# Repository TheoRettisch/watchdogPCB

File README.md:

# DSP Heartbeat Watchdog Board

## Purpose

This experimental board switches the 12 V amplifier remote output in a car PC
audio system. A 3.3 V heartbeat from the DSP keeps a hardware timer armed, a
separate fault input can disable the output, and an isolated sense line reports
the voltage state back to the DSP.

## Before You Build or Connect

Use an upstream fuse on the 12 V input. F1 is a resettable PTC that limits
current on the remote output. Review the behavior below and bench-test the
board before connecting an amplifier. See the [Bring-Up Checklist](#bring-up-checklist)
and [Known Limitations](#known-limitations).

### Connector Summary

| Connector | Pin or terminal | Net | Function |
|---|---|---|---|
| J1 | Pin 1 | `DSP_HB_3V3` | 3.3 V heartbeat from the DSP |
| J1 | Pin 2 | `DSP_GND` | Shared DSP-side return for heartbeat, fault, and sense |
| J2 | Pin 1 | `DSP_FAULT_IN` | Fault GPIO, driven low when healthy |
| J2 | Pin 2 | `DSP_3V3` | 3.3 V supply for the fault and sense pullups |
| J3 | Pin 1 | `+12V` | Fused 12 V input |
| J3 | Pin 2 | `CAR_GND` | Car or bench supply ground |
| J4 | Single wire entry | `AMP_REM` | Switched amplifier remote output |
| J5 | Single wire entry | `REMOTE_SENSE` | Active-low voltage feedback to the DSP |

J1 pin 2 is the board's only connector for `DSP_GND`. J4 and J5 each use a
Phoenix 1790490 terminal with one wire entry and two PCB solder tails on the
same net. The amplifier remote input uses the amplifier's own ground return.

### Enable and Shutdown Behavior

| Condition | Heartbeat timer | Fault clamp |
|---|---|---|
| Heartbeat edges arrive within the timeout and the fault GPIO is low | Keeps the output driver enabled | Inactive |
| Pulses stop or J1 pin 1 opens while J1 pin 2 stays connected | Switches J4 off when the timer expires | Remains available with DSP supply and ground intact |
| Fault GPIO goes high or Hi-Z, or its signal wire opens, with `DSP_3V3` and `DSP_GND` intact | Continues to follow heartbeat edges | U2 clamps the driver and switches J4 off |
| Control process crashes or exits, or the DSP reboots | Times out if heartbeat edges stop | Depends on the GPIO state. A pin still driving low leaves the clamp inactive |
| **J1 ground return opens**, including when both J1 wires are disconnected | Times out after the last trigger | Loss of `DSP_GND` can release an active clamp and briefly turn J4 on while the timer is still armed |
| **Complete J2 disconnection**, with on-board R12 as the only pullup on J5 | Can keep J4 on as long as heartbeat edges continue | U2 loses its input drive and any active clamp releases |
| Board unpowered or `+5V` absent | Timer inactive. R9 defaults Q1 off | — |
| Heartbeat held high at power-on, fault clamp inactive | Reset release can trigger one output pulse. See [Hardware Timeout](#hardware-timeout) | Inactive |

With J2 disconnected and U3 off, an additional pullup on J5, including the
DSP GPIO's internal pullup, can feed the U2 LED through R12, R10, and R11.
Whether that current can hold the fault clamp active depends on the pullup
strength.

## Project Status and Publication Scope

The author designed and hand-assembled REV 01 for a private installation and
shares the design free of charge. No boards, kits, or services are offered. The
design is licensed under `CERN-OHL-S-2.0`, which allows commercial use under its
terms. See [License](#license) and [Validation Status and Scope](#validation-status-and-scope).

## Project Files

- [KiCad project](dhw.kicad_pro), [schematic](dhw.kicad_sch), and [PCB layout](dhw.kicad_pcb)
- [Bill of materials](dhw.csv) with part numbers and datasheet links where available
- [Project footprints](libs/Watchdog.pretty/) for the Bourns MF-R025 and Phoenix Contact 1790490
- [Hand-built SPICE testbenches](spice/testbenches/) and [auto-generated runs](spice_runs/)

Open the project in KiCad 10 with the standard symbol and footprint libraries
installed. All schematic symbols use the standard libraries. The
[footprint library table](fp-lib-table) resolves the two local footprints
through `${KIPRJMOD}`. Those footprints reference optional STEP models under
`libs/3D_models/` that are absent from this checkout.

The companion watchdog software is maintained separately. See
[Timing Notes](#timing-notes) for the heartbeat settings used for this design

## High-Level Architecture

```mermaid
flowchart LR
    DSP["Lattepanda / DSP side\n3.3 V GPIO heartbeat"] --> J1["J1 heartbeat input"]
    J1 --> U1["U1 LTV-817\nheartbeat optocoupler"]
    U1 --> IC1["IC1 CD74HC123E\nretriggerable monostable"]
    IC1 --> Q2["Q2 2N3904\nbase/gate driver"]
    Q2 --> Q1["Q1 FQP27P06\nP-channel high-side switch"]
    Q1 --> F1["F1 MF-R025 PTC"]
    F1 --> J4["J4 amplifier remote output"]

    DSPF["DSP fault GPIO\nlow = healthy"] --> J2["J2 fault input and 3.3 V supply"]
    J2 --> U2["U2 LTV-817\nfault optocoupler"]
    U2 --> Q2

    F1 --> R13["R13 2.2 kohm"]
    R13 --> U3["U3 LTV-817\nsense optocoupler"]
    U3 --> J5["J5 remote sense output"]
    J5 --> DSPS["DSP sense GPIO\nlow = voltage detected"]

    J3["+12 V input"] --> D1["D1 P6KE22A TVS"]
    J3 --> U4["U4 L7805CV\n+5 V logic rail"]
    U4 --> IC1
```

## Functional Description

### Heartbeat Input Path

R2 (680 Ω) limits the U1 optocoupler LED current. R1 (100 kΩ) pulls the
heartbeat input low when the drive floats. When the DSP GPIO pulse goes
high, U1 pulls `HB_ISO_LOW` low on the car-ground side. R7 (47 kΩ) pulls
that node up to `+5V` between pulses. The falling edge triggers IC1.

### Hardware Timeout

IC1 is a CD74HC123E retriggerable monostable. The first monostable section is
used as the heartbeat watchdog timer.

The first section uses the following IC1 pins.

- pin 1, `~1A`: heartbeat trigger input, net `HB_ISO_LOW`
- pin 2, `1B`: tied to `+5V`
- pin 3, `~1R`: power-on reset network R5/C4 (see below)
- pin 13, `1Q`: watchdog output, net `MONO_Q`
- pin 14, `1CX`: timing capacitor node
- pin 15, `1RXCX`: timing resistor/capacitor node
- pin 16, `VCC`: `+5V`
- pin 8, `GND`: `CAR_GND`

The inputs and timing pins of the second section (`~2A`, `2B`, `~2R`, `2CX`,
and `2RXCX`) are tied to `CAR_GND`, holding it in reset. The unused outputs
(`~1Q`, `2Q`, and `~2Q`) carry no-connect flags.

R6 (220 kΩ) and C1 (1 µF, 63 V film, WIMA MKS2C041001F00JSSD) set the
nominal timeout. See [Timing Notes](#timing-notes) for the calculation and
other R6 values.

R5 (200 kΩ) and C4 (100 nF) hold `~1R` low at power-on while C4 charges. If
the heartbeat GPIO is already held high, U1 holds `~1A` low while `1B` is
high. The CD74HC123 can trigger as reset rises under those conditions. If
the fault clamp is inactive, J4 can energize for one timeout without a new
heartbeat edge. See the truth table in the
[TI CD74HC123 datasheet](https://www.ti.com/lit/ds/symlink/cd74hc123.pdf#page=2).

### Fault Input Path

The DSP is intended to drive `DSP_FAULT_IN` low only while healthy and
intentionally armed. When the GPIO floats or its signal wire opens, the
3.3 V supply feeds the U2 optocoupler LED through the R10 pullup (680 Ω) and
R11 (330 Ω). A GPIO driven high supplies current through R11 directly. With
a 1.2 V LED drop, these paths give about 2.1 mA and 6.4 mA respectively at
3.3 V.

U2 pulls `Q2_BASE` low and turns off the output driver even while the
monostable is active. Its input LED returns through `DSP_GND` on J1 pin 2.
See [Enable and Shutdown Behavior](#enable-and-shutdown-behavior) for the
effects of connector and GPIO faults.

### Remote Output Driver

The amplifier remote output is switched by Q1, a P-channel MOSFET used as a
high-side switch.

- Q1 FQP27P06
  - pad 1: gate, net `Q1_GATE`
  - pad 2: drain, net `Q1_DRAIN`
  - pad 3: source, net `+12V`
- Q2 2N3904 pulls the Q1 gate low when `MONO_Q` is high and U2 is inactive
  - pad 1: emitter, `CAR_GND`
  - pad 2: base, `Q2_BASE`
  - pad 3: collector, `Q2_COLL`
- R4: 47 kohm base feed from `MONO_Q` into Q2
- R3: 100 kohm base pulldown on `Q2_BASE`
- R9: 100 kohm gate pullup to `+12V`, defaulting Q1 off
- R8: 10 kohm between Q1 gate and Q2 collector
- Z1 BZX55C12-TAP clamps Q1 gate-source voltage
  - cathode to `+12V`
  - anode to `Q1_GATE`
- F1 MF-R025 PTC is in series with the remote output
  - F1 pin 1: `Q1_DRAIN`
  - F1 pin 2: `AMP_REM`

J4 exposes `AMP_REM` through its single wire entry. When Q2 is off, R9
returns the Q1 gate to the source rail and turns Q1 off.

### Remote Sense Feedback

R13 (2.2 kΩ) feeds the U3 optocoupler LED from `AMP_REM` after F1 (about
4.9 mA at 12 V). D2 (1N4148) clamps reverse voltage across the LED, with its
cathode at the R13/U3 node and its anode at `CAR_GND`.

J5's single wire entry carries `REMOTE_SENSE`. With `DSP_3V3` and `DSP_GND`
present, U3's open collector pulls J5 low when the post-F1 voltage is high
enough to drive the optocoupler. R12 (10 kΩ) pulls J5 high when U3 releases
it. Software can flag a mismatch between the commanded state and this
voltage indication. A tripped F1 is one possible cause of low output voltage.
The board itself takes no action based on the sense line.

Treat sense as unavailable if the DSP supply or ground is lost. With J2
unplugged and U3 off, R12 has no supply to drive J5 high, so the reading can
float or follow the receiving GPIO's bias.

## Power Architecture

- D1 (P6KE22A) clamps transients on the 12 V input. Pad 1 is the cathode on
  `+12V` and pad 2 is the anode on `CAR_GND`.
- U4 (L7805CV) generates the local `+5V` logic rail. Pins 1 through 3 are
  `+12V`, `CAR_GND`, and `+5V` respectively.
- C2 (10 µF, 63 V polymer hybrid, Würth 870575873001) provides bulk capacitance
  on `+5V`.
- C6 (470 nF, 50 V) bypasses the U4 input. C3 (100 nF) bypasses its output.
- C5 and C7 (100 nF each) bypass the IC1 supply and the 12 V switch stage,
  respectively. C4 (100 nF) belongs to the reset circuit.

C3–C7 are 1206 SMD ceramics. The other electrical components are through-hole.

## Timing Notes

The companion configuration uses 20 Hz (one trigger edge every 50 ms), a 5 ms
pulse width, and a 70 ms software jitter warning threshold. The hardware
needs one clean trigger edge per period. The software warning is a diagnostic
that depends on the process running.

At 5 V, the CD74HC123 nominal pulse width is approximately
`0.45 × R6 × C1`. With the installed 220 kΩ and 1 µF, the calculation gives
99 ms, leaving about 49 ms of nominal margin at 20 Hz. The back silkscreen
lists these R6 options for other heartbeat intervals (C1 remains 1 µF).

| Heartbeat | Period | Nominal margin with 220 kΩ | Silkscreen R6 options | Nominal timeout with those options |
|---:|---:|---:|---|---|
| 50 Hz | 20 ms | 79 ms | 91 / 130 kΩ | 41 / 59 ms |
| 25 Hz | 40 ms | 59 ms | 180 / 270 kΩ | 81 / 122 ms |
| 20 Hz | 50 ms | 49 ms | 220 / 330 kΩ | 99 / 149 ms |
| 15 Hz | 66.7 ms | 32 ms | 300 / 430 kΩ | 135 / 194 ms |
| 10 Hz | 100 ms | None | 470 / 680 kΩ | 212 / 306 ms |

Trigger gaps must stay below the actual timeout. Allow for R6/C1 tolerance,
temperature, supply variation, and scheduling jitter when selecting the
heartbeat rate and checking the assembled board.

## PCB / Fabrication Details

- Board size is 72.0 mm × 64.0 mm with two copper layers. Separate `CAR_GND`
  and `DSP_GND` pours appear on both sides.
- The layout has 31 through-hole components, five 1206 components, and four
  3.2 mm non-plated M3 mounting holes.
- The board routes 24 nets and uses 48 vias (0.60 mm diameter, 0.30 mm drill),
  mostly for ground stitching.
- The project specifies a 0.20 mm minimum track width, a 0.30 mm minimum
  through-hole drill, and a 0.15 mm minimum via annular ring.

Order bare boards for hand assembly. Typical settings are 2-layer FR-4,
1.6 mm thickness, 1 oz copper, ENIG or lead-free HASL, and electrical testing.

## Validation Status and Scope

### Saved Simulations

| Testbench | Scope and saved result |
|---|---|
| [Monostable RC model](spice/testbenches/tb_monostable_timeout.cir) | Uses the older 200 kΩ R6 and 1 µF C1. The simulated RC interval after the last discharge ends is about 90 ms. The 99 ms for the current 220 kΩ value is a nominal calculation. |
| [Gate driver](spice/testbenches/tb_gate_driver.cir) | With a generic MOSFET, an idealized Q2 switch, and a cold F1, the model gives about 10.9 V from source to gate when enabled at 12 V. |
| [Optocoupler LED drive](spice/testbenches/tb_opto_led_drive.cir) | A generic IR LED with a 680 Ω series resistor draws about 3.1 mA at 3.3 V. The model covers the U1 LED drive. It omits the U2 fault clamp and U3 sense path. |

See [Known Limitations](#known-limitations) for the hardware validation scope.

## Bring-Up Checklist

### Bench Checks

1. With the amplifier disconnected, inspect solder joints and verify diode
   and transistor orientation. D1's cathode goes to `+12V`. D2's cathode goes
   to the R13/U3 node. Q1 pads 1 through 3 are gate, drain, and source.
2. Connect the DSP supply and ground per the [connector table](#connector-summary).
   Hold the heartbeat and fault GPIOs low. Apply fused, current-limited 12 V
   to J3. Confirm U4 supplies about 5 V and J4 remains off.
3. Switch off the 12 V supply and let the board power down. Keep the fault
   GPIO low and hold the heartbeat GPIO high before reapplying 12 V. Observe
   J4 relative to `CAR_GND` on an oscilloscope and check for a brief enable
   pulse as reset releases. Return the heartbeat GPIO to low before continuing.
4. Apply the 20 Hz heartbeat and confirm J4 turns on and J5 goes low. Stop
   the pulses, measure the interval from the last trigger edge to J4 turning
   off, and confirm J5 returns high. Compare the measured interval with the
   99 ms nominal value.
5. With the heartbeat running and the DSP supply and ground connected, drive
   the fault GPIO high, then test it in Hi-Z. Confirm J4 turns off in both
   cases. Restore the healthy state between tests.
6. Test the wire-loss and full-disconnection cases in the
   [enable and shutdown table](#enable-and-shutdown-behavior). Restore the
   wiring between cases.

   - For J1 ground loss, reference the J4 scope probe to `CAR_GND` and
     verify that test equipment provides no alternate `DSP_GND` return.
     Run the heartbeat, assert the fault, and confirm J4 is off. With the
     timer still armed, use an inline switch to open J1 pin 2 while leaving
     pin 1 connected. Watch for a brief J4 pulse as the clamp releases.
   - For complete J2 disconnection, remove or disable any additional J5
     pullup to reproduce the table case. If the installation uses a pullup,
     repeat the test with that pullup in place.

7. Repeat with a representative dummy load and record the results before
   connecting an amplifier.

### Software Checks

- If using `camilladsp_watchdog.py`, confirm it logs `hb_gap_ms`, `hb_max_ms`,
  and `hb_missed`. Stress the Linux system and check that observed heartbeat
  gaps stay below the 70 ms warning threshold and the measured hardware timeout.
- Observe the real GPIO states during boot, shutdown, and process exit or
  failure. Verify task supervision stops the heartbeat or asserts the fault
  when the monitor task fails.
- Compare `REMOTE_SENSE` with the commanded output state and flag a mismatch
  while the DSP supply and ground are present. Treat the reading as unavailable
  when either connection is lost.

## Known Limitations

- The board has no automotive certification. The repository records no
  measurements of assembled hardware and no EMC, load-dump, reverse-polarity,
  jump-start, vibration, thermal-cycling, or lifetime tests.
- D1 is a transient clamp. Load-dump and reverse-polarity protection are
  outside the design scope.
- U1, U2, and U3 provide functional signal isolation between `DSP_GND` and
  `CAR_GND` in a 12 V system. The grounds may share a return elsewhere in the
  installation. Use the isolation only for low-voltage signals.
- Reserve the 5 V rail for on-board loads. To probe the board, use component
  leads and connector pins because there are no dedicated test points.

## Revision Notes

- PCB silkscreen identifies the board as `DSP HEARTBEAT WATCHDOG`, `REV 01`.
- Current schematic note says the heartbeat source is `+3.3V`, `20 Hz`,
  `Lattepanda Mu`.
- The board carries a front-silk truth table and timeout formula, a back-silk
  R6 tuning table per heartbeat rate, the Q1 pinout legend, connector function
  labels, ground-domain markings, and a QR code. The stuck-level entries on
  the truth table describe behavior after the timeout. See
  [Hardware Timeout](#hardware-timeout) for power-on behavior.

## License

This hardware design is licensed under the CERN Open Hardware Licence Version
2, Strongly Reciprocal (`CERN-OHL-S-2.0`). See the full text in
[`LICENSE`](LICENSE).

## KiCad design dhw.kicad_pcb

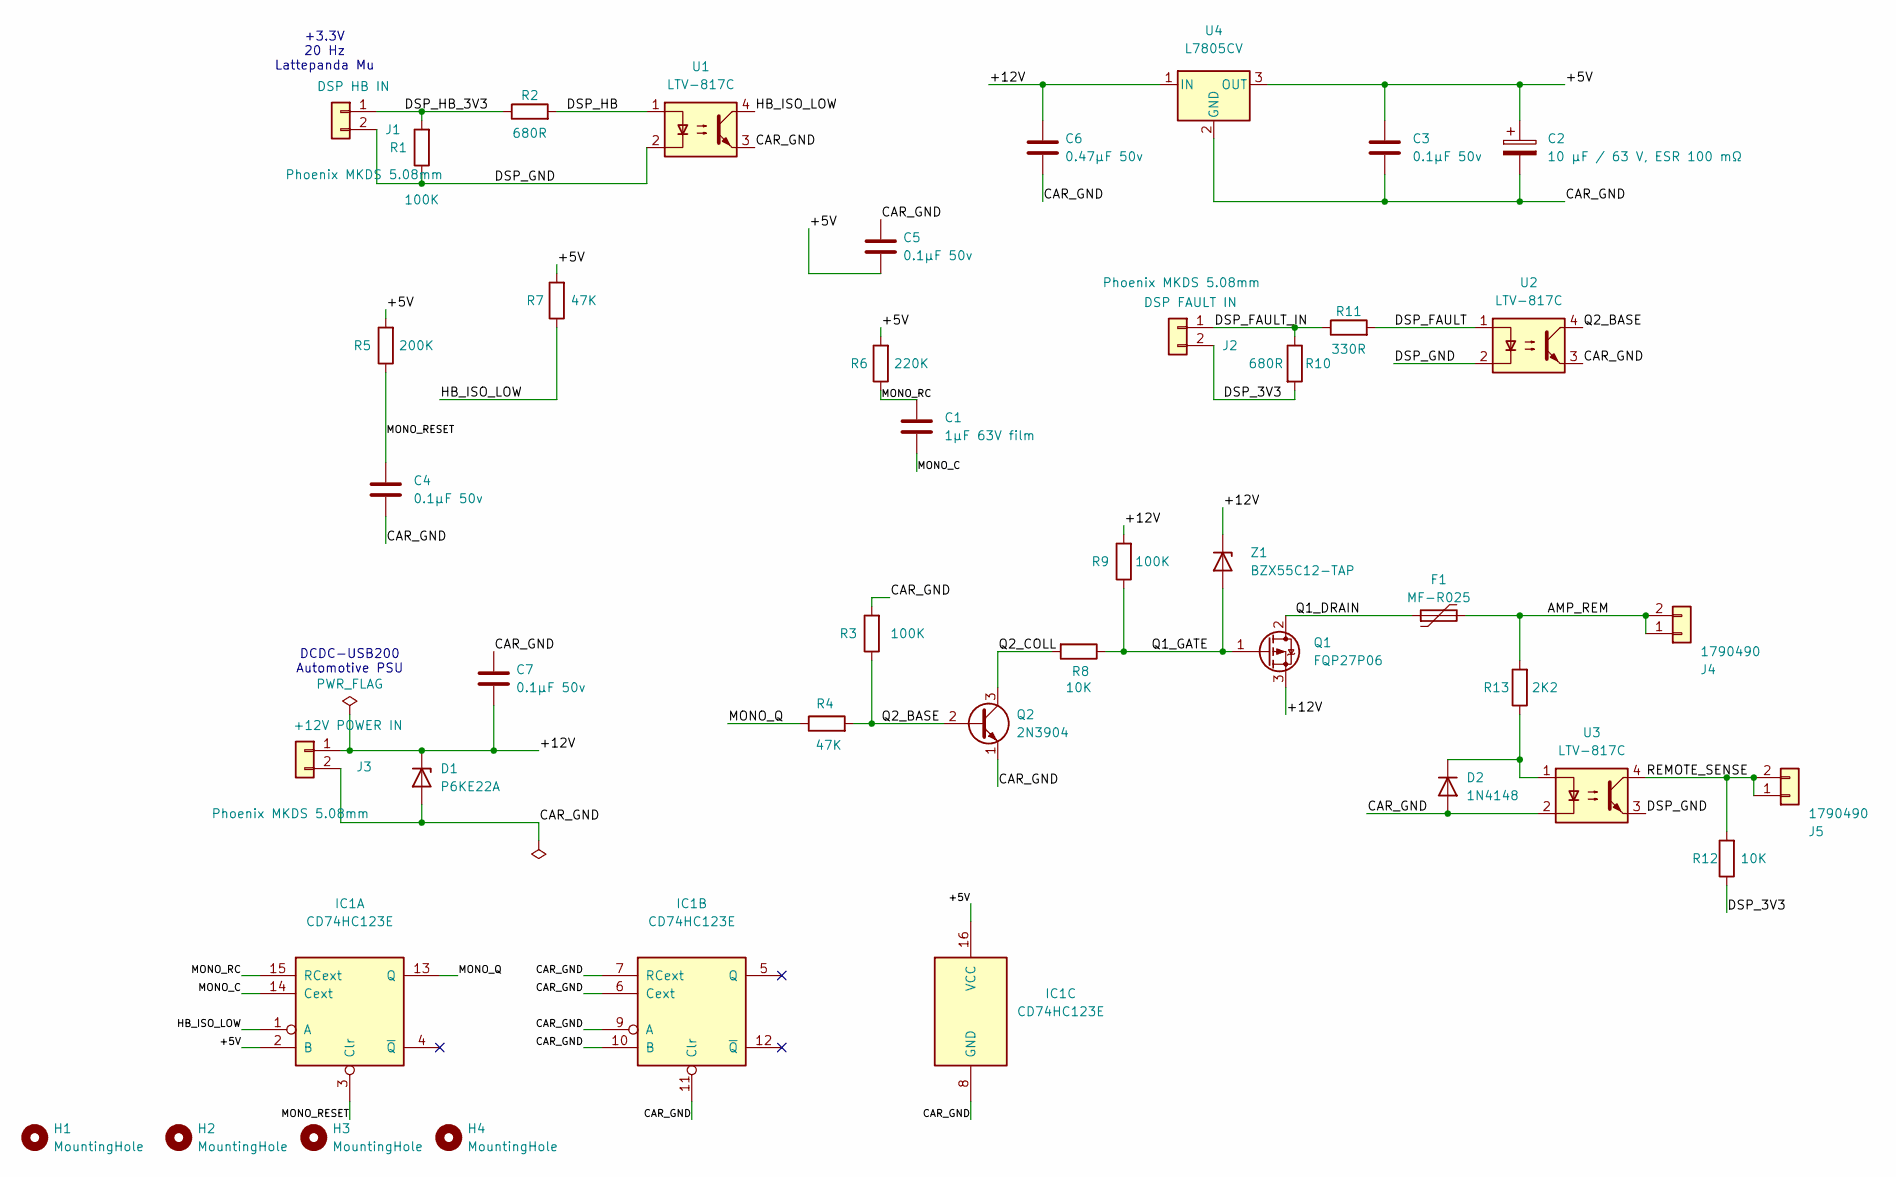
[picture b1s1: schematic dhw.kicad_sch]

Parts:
C1: 1µF 63V film; C_Rect_L7.2mm_W5.0mm_P5.00mm; Mouser Part Number 505-MKS21.0/63/5
C2: 10 µF / 63 V, ESR 100 mΩ; CP_Radial_D6.3mm_P2.50mm; Mouser Part Number 710-870575873001
C3, C4, C5, C7: 0.1µF 50v; C_1206_3216Metric_Pad1.33x1.80mm_HandSolder; MPN CGA5L2C0G1H104J160AA
C6: 0.47µF 50v; C_1206_3216Metric_Pad1.33x1.80mm_HandSolder; MPN 885012208091
D1: P6KE22A; D_DO-15_P10.16mm_Horizontal; MPN P6KE22A
D2: 1N4148; D_DO-35_SOD27_P7.62mm_Horizontal; MPN 1N4148
F1: MF-R025; Fuse_Bourns_MF-R025_P5.10mm; Mouser Part Number 652-MFR025
H1, H2, H3, H4: MountingHole; MountingHole_3.2mm_M3
IC1: CD74HC123E; DIP-16_W7.62mm; Mouser Part Number 595-CD74HC123E
J1: DSP HB IN; TerminalBlock_Phoenix_MKDS-1,5-2-5.08_1x02_P5.08mm_Horizont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; MPN 1715721
J2: DSP FAULT IN; TerminalBlock_Phoenix_MKDS-1,5-2-5.08_1x02_P5.08mm_Horizont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; MPN 1715721
J3: +12V POWER IN; TerminalBlock_Phoenix_MKDS-1,5-2-5.08_1x02_P5.08mm_Horizont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; MPN 1715721
J4, J5: 1790490; TerminalBlock_Phoenix_FFKDSA1-V1-7.62_1x01_2SolderPins; Mouser Part Number 651-1790490
Q1: FQP27P06; TO-220-3_Vertical; MPN FQP27P06
Q2: 2N3904; TO-92_Inline_Wide; MPN 2N3904
R1, R3, R9: 100K; R_Axial_DIN0207_L6.3mm_D2.5mm_P7.62mm_Horizontal; MPN MFR-25FRF52-100K
R2, R10: 680R; R_Axial_DIN0207_L6.3mm_D2.5mm_P7.62mm_Horizontal; MPN MFR-25FRF52-680R
R4, R7: 47K; R_Axial_DIN0207_L6.3mm_D2.5mm_P7.62mm_Horizontal; MPN MFR-25FRF52-47K
R5: 200K; R_Axial_DIN0207_L6.3mm_D2.5mm_P7.62mm_Horizontal; MPN MFR-25FRF52-200K
R6: 220K; R_Axial_DIN0207_L6.3mm_D2.5mm_P7.62mm_Horizontal; MPN MFR-25FRF52-220K
R8, R12: 10K; R_Axial_DIN0207_L6.3mm_D2.5mm_P7.62mm_Horizontal; MPN MFR-25FRF52-10K
R11: 330R; R_Axial_DIN0207_L6.3mm_D2.5mm_P7.62mm_Horizontal; MPN MFR-25FRF52-330R
R13: 2K2; R_Axial_DIN0207_L6.3mm_D2.5mm_P7.62mm_Horizontal; MPN MFR-25FRF52-2K2
U1, U2, U3: LTV-817C; DIP-4_W7.62mm; MPN LTV-817C
U4: L7805CV; TO-220-3_Vertical; PARTREV 36
Z1: BZX55C12-TAP; D_DO-35_SOD27_P7.62mm_Horizontal; Mouser Part Number 78-BZX55C12-TAP

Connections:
/+5V: C2.1, C3.1, C5.2, IC1.2 (B), IC1.16 (VCC), R5.2, R6.2, R7.2, U4.3 (OUT)
/+12V: C6.1, C7.2, D1.1 (K), J3.1, Q1.3 (S), R9.2, U4.1 (IN), Z1.1 (K)
/AMP_REM: F1.2, J4.1, J4.2, R13.2
/CAR_GND: C2.2, C3.2, C4.2, C5.1, C6.2, C7.1, D1.2 (A), D2.2 (A), IC1.6 (Cext), IC1.7 (RCext), IC1.8 (GND), IC1.9 (A), IC1.10 (B), IC1.11 (Clr), J3.2, Q2.1 (E), R3.2, U1.3, U2.3, U3.2, U4.2 (GND)
/DSP_3V3: J2.2, R10.2, R12.1
/DSP_FAULT: R11.2, U2.1
/DSP_FAULT_IN: J2.1, R10.1, R11.1
/DSP_GND: J1.2, R1.1, U1.2, U2.2, U3.3
/DSP_HB: R2.2, U1.1
/DSP_HB_3V3: J1.1, R1.2, R2.1
/HB_ISO_LOW: IC1.1 (A), R7.1, U1.4
/MONO_C: C1.2, IC1.14 (Cext)
/MONO_Q: IC1.13 (Q), R4.1
/MONO_RC: C1.1, IC1.15 (RCext), R6.1
/MONO_RESET: C4.1, IC1.3 (Clr), R5.1
/Q1_DRAIN: F1.1, Q1.2 (D)
/Q1_GATE: Q1.1 (G), R8.1, R9.1, Z1.2 (A)
/Q2_BASE: Q2.2 (B), R3.1, R4.2, U2.4
/Q2_COLL: Q2.3 (C), R8.2
/REMOTE_SENSE: J5.1, J5.2, R12.2, U3.4
unnamed: D2.1 (K), R13.1, U3.1

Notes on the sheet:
DCDC-USB200 Automotive PSU
+3.3V 20 Hz Lattepanda Mu

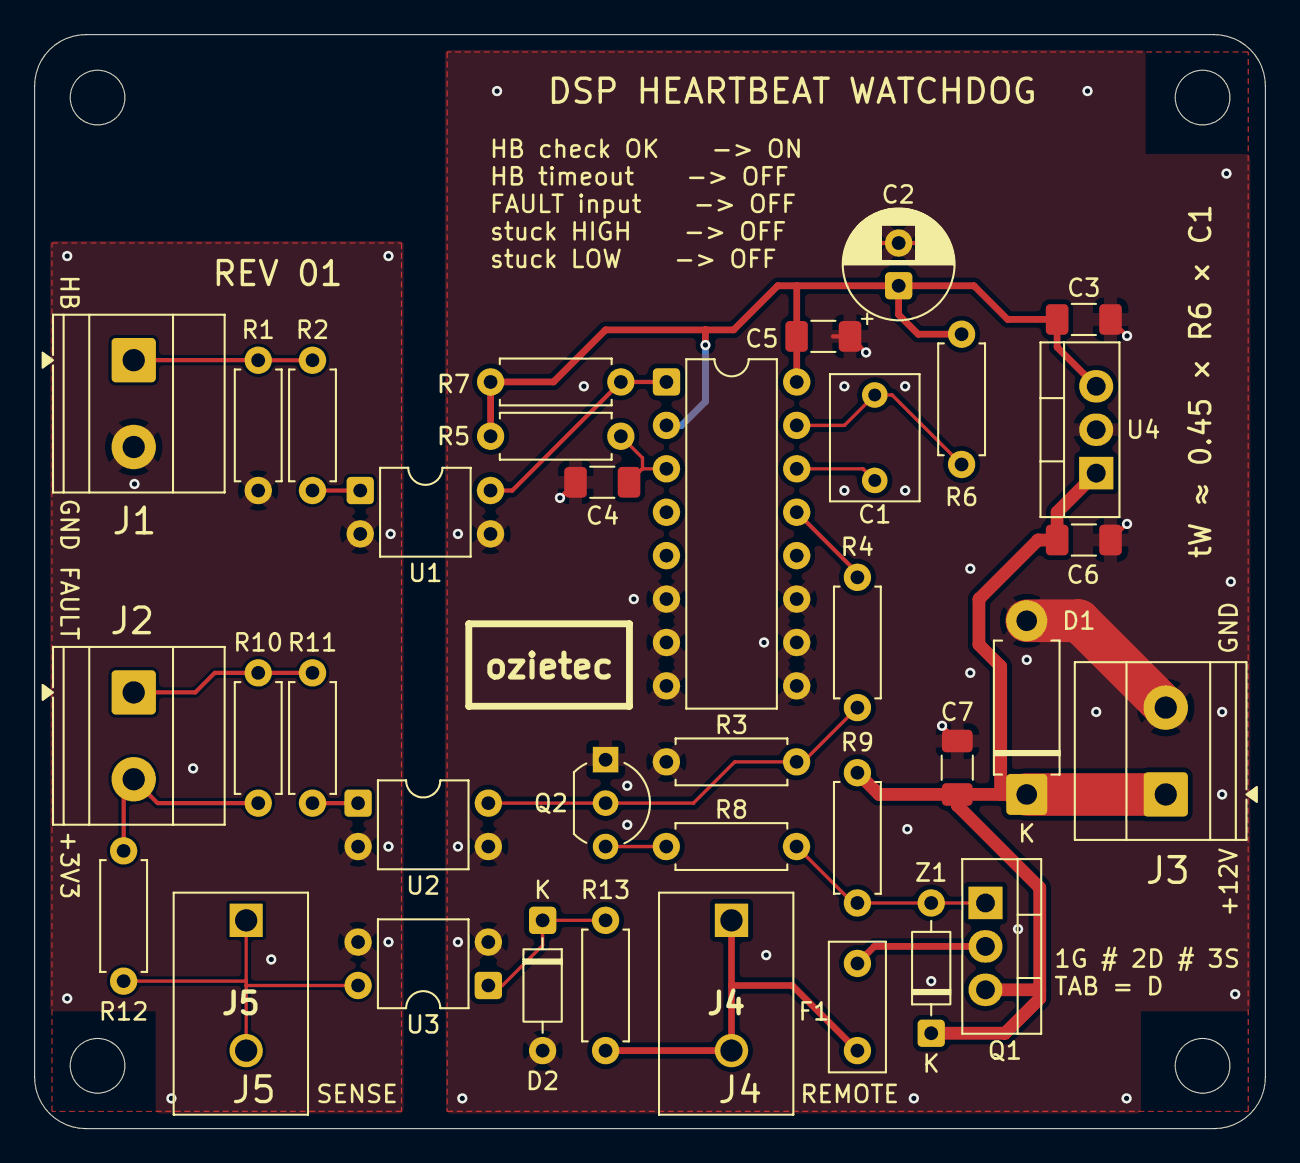
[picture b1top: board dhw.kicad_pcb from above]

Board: 2 copper layers, 72.0 x 64.0 mm, 40 parts (0 on the bottom side), 21 nets.
